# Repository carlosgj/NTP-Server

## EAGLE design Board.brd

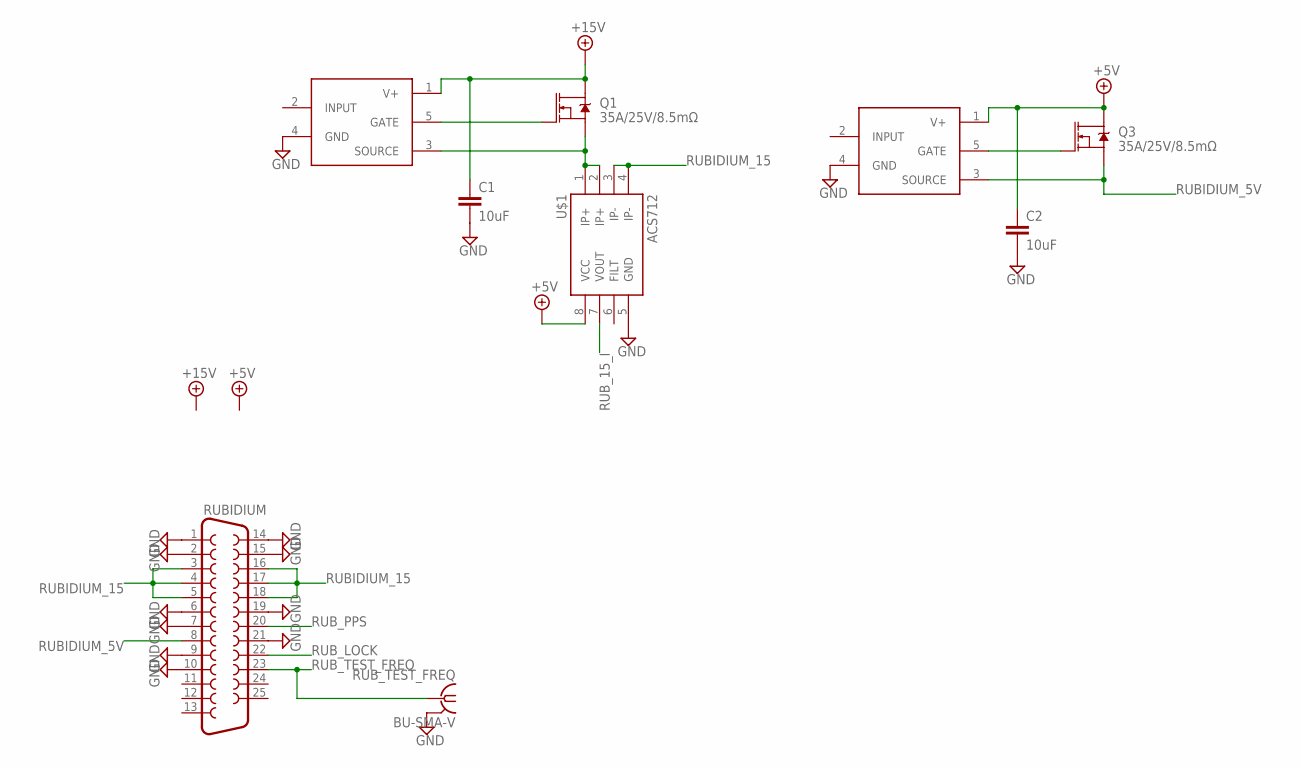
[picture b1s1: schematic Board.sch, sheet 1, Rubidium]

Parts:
C1, C2: 10uF; C1206
Q1, Q3: 35A/25V/8.5mΩ; DPAK
RUBIDIUM: F25VP
RUB_TEST_FREQ: BU-SMA-V
U$1: ACS712; SO08
U$3, U$4: MIC5014; SOIC8

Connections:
+5V: C2.1, Q3.4 (D), U$1.8 (VCC), U$4.1 (V+); also elsewhere on the board
+15V: C1.1, Q1.4 (D), U$3.1 (V+); also elsewhere on the board
GND: C1.2, C2.2, RUBIDIUM.1, RUBIDIUM.2, RUBIDIUM.6, RUBIDIUM.7, RUBIDIUM.9, RUBIDIUM.10, RUBIDIUM.14, RUBIDIUM.15, RUBIDIUM.19, RUBIDIUM.21, RUB_TEST_FREQ.2, RUB_TEST_FREQ.3 (2), RUB_TEST_FREQ.4 (2), RUB_TEST_FREQ.5 (2), U$1.5 (GND), U$3.4 (GND), U$4.4 (GND); also elsewhere on the board
unnamed: Q1.3 (S), U$1.1 (IP+), U$1.2 (IP+), U$3.3 (SOURCE)
unnamed: Q3.1 (G), U$4.5 (GATE)
unnamed: Q1.1 (G), U$3.5 (GATE)
RUBIDIUM_5V: Q3.3 (S), RUBIDIUM.8, U$4.3 (SOURCE)
RUBIDIUM_15: RUBIDIUM.3, RUBIDIUM.4, RUBIDIUM.5, RUBIDIUM.16, RUBIDIUM.17, RUBIDIUM.18, U$1.3 (IP-), U$1.4 (IP-)
RUB_15_I: U$1.7 (VOUT)
RUB_LOCK: RUBIDIUM.22
RUB_PPS: RUBIDIUM.20; also elsewhere on the board
RUB_TEST_FREQ: RUBIDIUM.23, RUB_TEST_FREQ.1

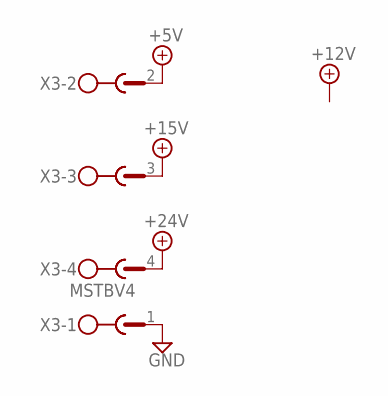
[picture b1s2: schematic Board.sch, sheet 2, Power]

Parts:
X3: MSTBV4

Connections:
+5V: X3.2; also elsewhere on the board
+15V: X3.3; also elsewhere on the board
+24V: X3.4; also elsewhere on the board
GND: X3.1; also elsewhere on the board

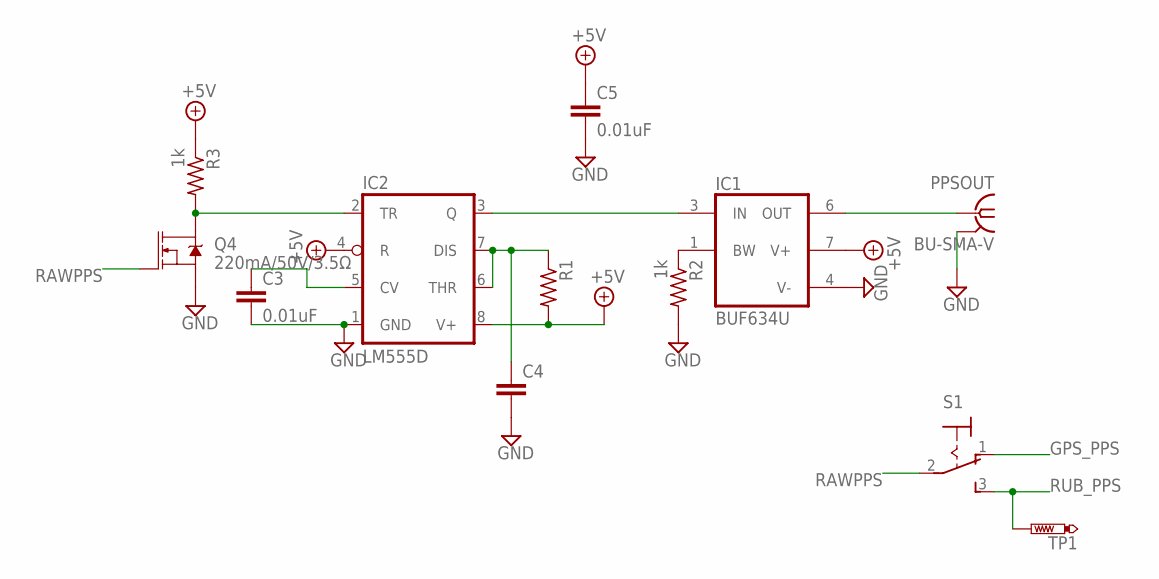
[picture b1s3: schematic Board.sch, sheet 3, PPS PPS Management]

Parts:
C3, C5: 0.01uF; C1206
C4: C-EUC1206; C1206
IC1: BUF634U; SO08
IC2: LM555D; SO08
PPSOUT: BU-SMA-V
Q4: 220mA/50V/3.5Ω; SOT23-3
R1: R-US_R1206; R1206
R2, R3: 1k; R1206
S1: M9040P
TP1: PTR1PAD1-13; P1-13

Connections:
+5V: C5.1, IC1.7 (V+), IC2.4 (R), IC2.8 (V+), R1.2, R3.1; also elsewhere on the board
GND: C3.2, C4.2, C5.2, IC1.4 (V-), IC2.1 (GND), PPSOUT.2, PPSOUT.3 (2), PPSOUT.4 (2), PPSOUT.5 (2), Q4.2 (S), R2.2; also elsewhere on the board
GPS_PPS: S1.1 (O)
unnamed: IC1.6 (OUT), PPSOUT.1
unnamed: IC1.3 (IN), IC2.3 (Q)
unnamed: C4.1, IC2.6 (THR), IC2.7 (DIS), R1.1
unnamed: C3.1, IC2.5 (CV)
unnamed: IC1.1 (BW), R2.1
unnamed: IC2.2 (TR), Q4.3 (D), R3.2
RAWPPS: Q4.1 (G), S1.2
RUB_PPS: S1.3 (S), TP1.TP; also elsewhere on the board

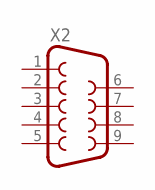
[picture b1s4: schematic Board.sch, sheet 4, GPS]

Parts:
X2: F09VP

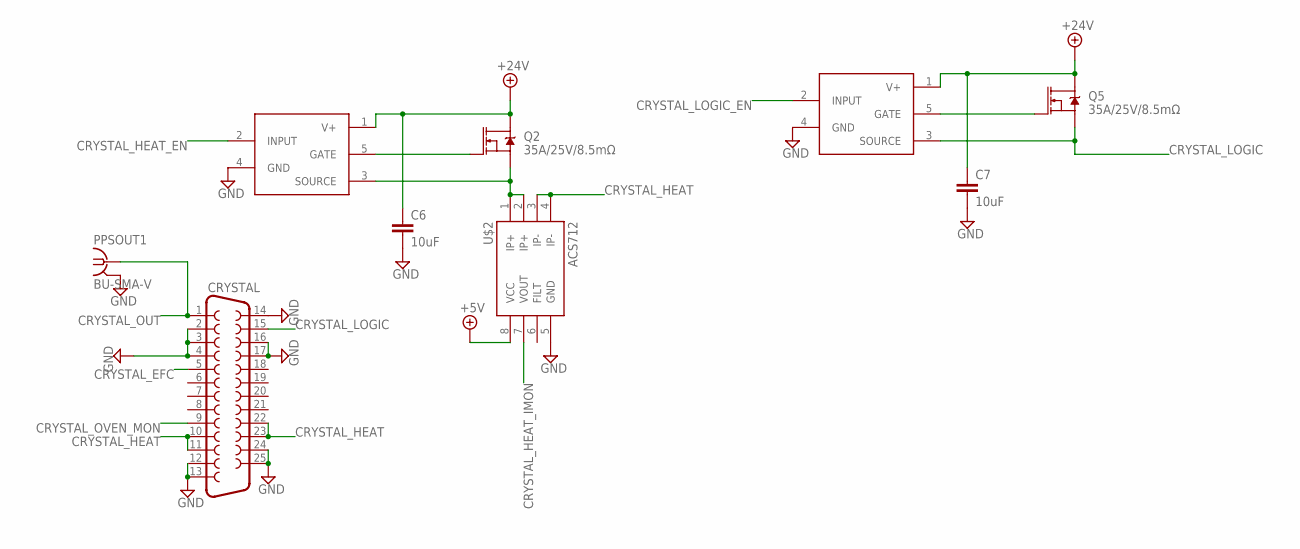
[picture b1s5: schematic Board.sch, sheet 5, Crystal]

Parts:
C6, C7: 10uF; C1206
CRYSTAL: F25VP
PPSOUT1: BU-SMA-V
Q2, Q5: 35A/25V/8.5mΩ; DPAK
U$2: ACS712; SO08
U$5, U$8: MIC5014; SOIC8

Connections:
+5V: U$2.8 (VCC); also elsewhere on the board
+24V: C6.1, C7.1, Q2.4 (D), Q5.4 (D), U$5.1 (V+), U$8.1 (V+); also elsewhere on the board
CRYSTAL_EFC: CRYSTAL.5
CRYSTAL_HEAT: CRYSTAL.10, CRYSTAL.11, CRYSTAL.22, CRYSTAL.23, U$2.3 (IP-), U$2.4 (IP-)
CRYSTAL_HEAT_EN: U$5.2 (INPUT)
CRYSTAL_HEAT_IMON: U$2.7 (VOUT)
CRYSTAL_LOGIC: CRYSTAL.15, Q5.3 (S), U$8.3 (SOURCE)
CRYSTAL_LOGIC_EN: U$8.2 (INPUT)
CRYSTAL_OUT: CRYSTAL.1, PPSOUT1.1
CRYSTAL_OVEN_MON: CRYSTAL.9
GND: C6.2, C7.2, CRYSTAL.2, CRYSTAL.3, CRYSTAL.4, CRYSTAL.12, CRYSTAL.13, CRYSTAL.14, CRYSTAL.16, CRYSTAL.17, CRYSTAL.24, CRYSTAL.25, PPSOUT1.2, PPSOUT1.3 (2), PPSOUT1.4 (2), PPSOUT1.5 (2), U$2.5 (GND), U$5.4 (GND), U$8.4 (GND); also elsewhere on the board
unnamed: Q2.3 (S), U$2.1 (IP+), U$2.2 (IP+), U$5.3 (SOURCE)
unnamed: Q2.1 (G), U$5.5 (GATE)
unnamed: Q5.1 (G), U$8.5 (GATE)

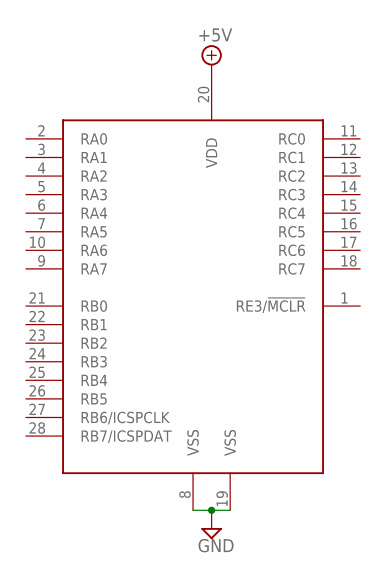
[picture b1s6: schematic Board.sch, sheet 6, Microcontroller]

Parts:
U$6: PIC18F25K42SOIC; SO28W

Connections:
+5V: U$6.20 (VDD); also elsewhere on the board
GND: U$6.8 (VSS), U$6.19 (VSS); also elsewhere on the board

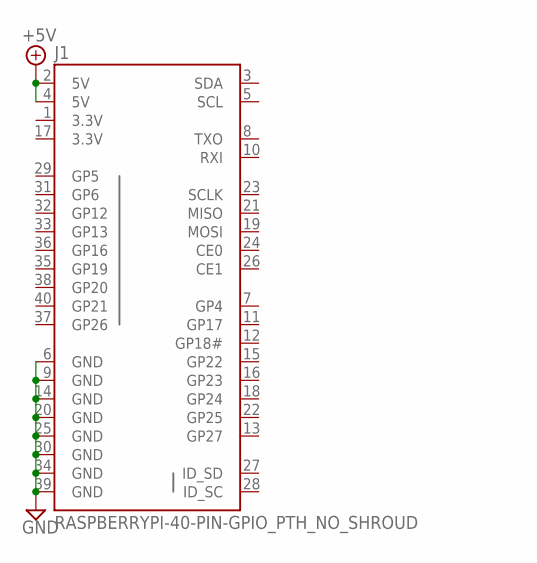
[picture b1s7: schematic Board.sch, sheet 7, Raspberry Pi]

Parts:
J1: RASPBERRYPI-40-PIN-GPIO_PTH_NO_SHROUD; 2X20

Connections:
3.3V: J1.1 (3.3V), J1.17 (3.3V)
+5V: J1.2 (5V), J1.4 (5V); also elsewhere on the board
GND: J1.6 (GND), J1.9 (GND), J1.14 (GND), J1.20 (GND), J1.25 (GND), J1.30 (GND), J1.34 (GND), J1.39 (GND); also elsewhere on the board

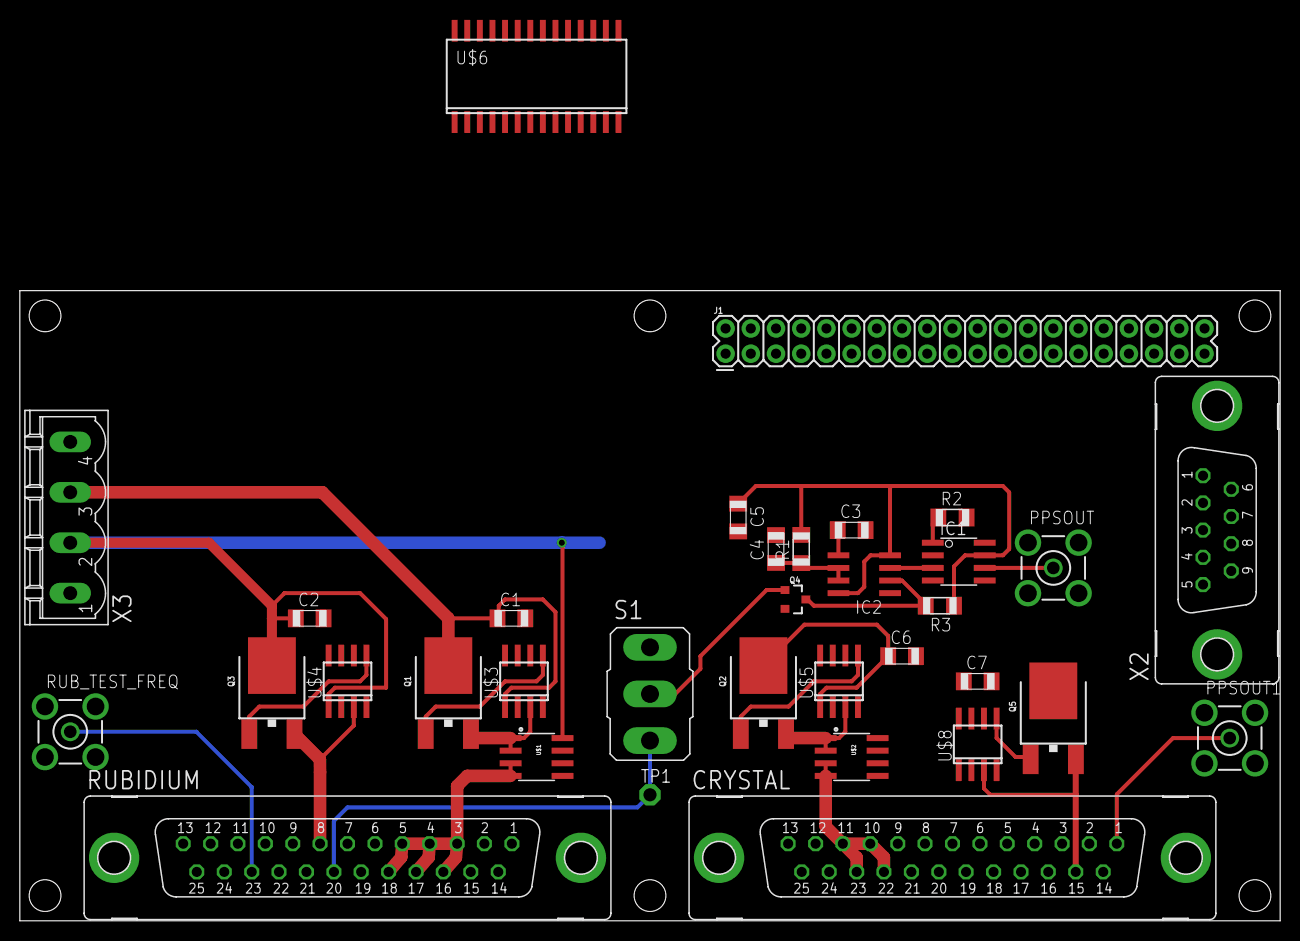
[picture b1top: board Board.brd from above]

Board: 2 copper layers, 127.0 x 63.5 mm, 34 parts (0 on the bottom side), 25 nets.

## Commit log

2019-08-15 Some specs
2020-10-08 Work
2020-10-09 Specs work
2020-10-09 Additional info
2020-10-09 Oops
2020-10-12 Schematic work
2020-10-12 Spec update
2020-10-13 PCB work
2020-10-13 Updating pin mappings
2020-11-28 Adding crystal
2020-12-02 Specs update

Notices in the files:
parts and their libraries:
SparkFun-Sensors: Licensing: Creative Commons ShareAlike 4.0 International - https://creativecommons.org/licenses/by-sa/4.0
